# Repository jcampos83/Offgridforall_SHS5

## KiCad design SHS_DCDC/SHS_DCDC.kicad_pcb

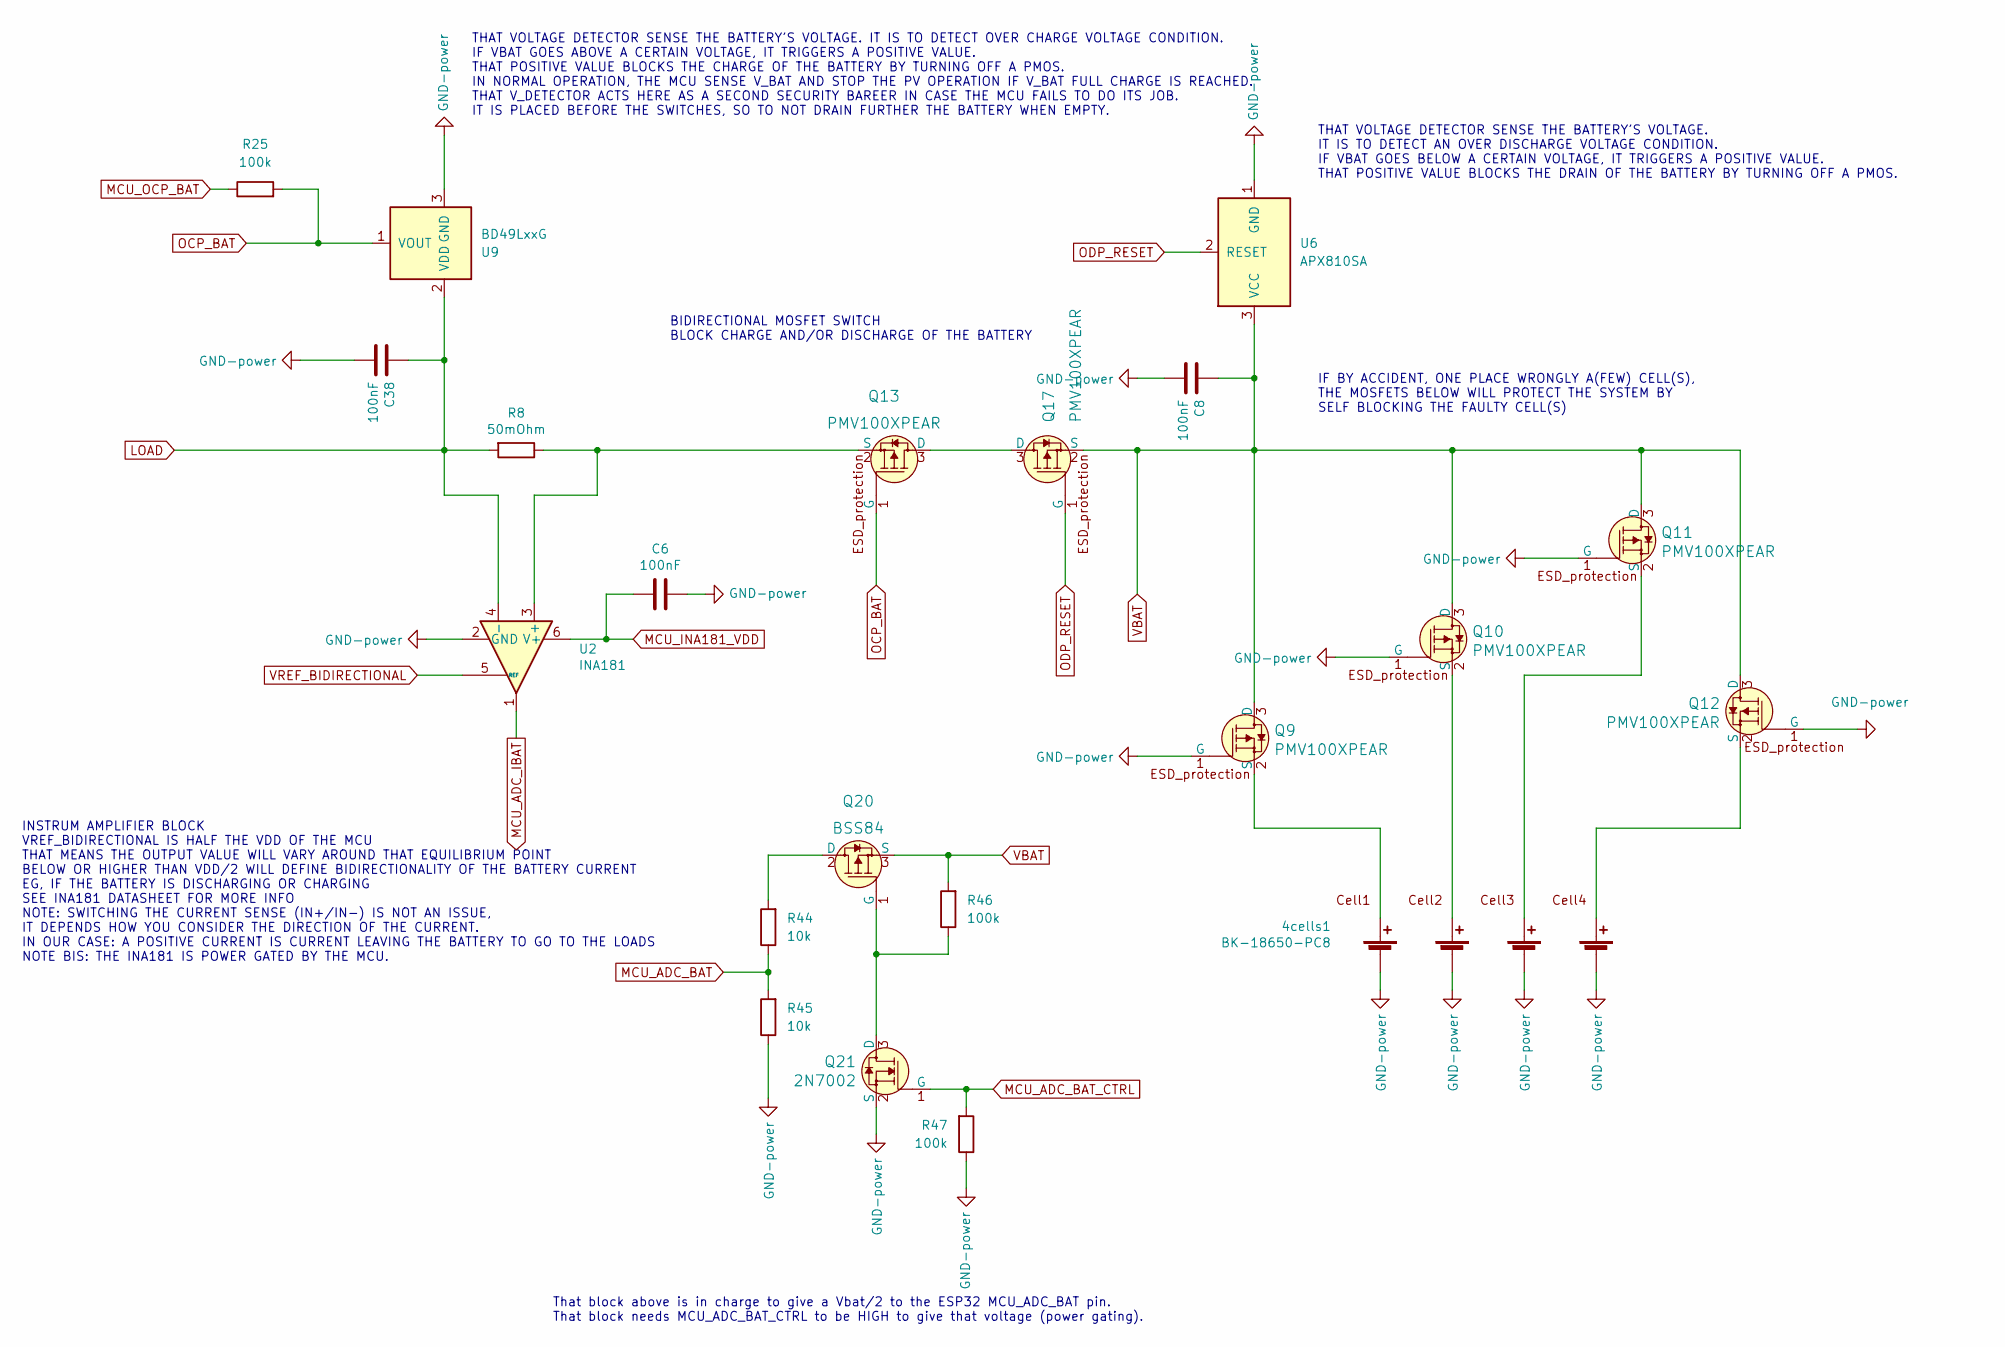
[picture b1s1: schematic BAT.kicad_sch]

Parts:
4cells1: BK-18650-PC8
C6, C8, C38: 100nF; C_0402_1005Metric
Q9, Q10, Q11, Q12, Q13, Q17: PMV100XPEAR; SOT-23-3; MPN PMV100XPEAR
Q20: BSS84; SOT-23; MPN BSS84; Digi-Key_PN BSS84CT-ND
Q21: 2N7002; SOT-23; MPN 2N7002; Digi-Key_PN 2N7002NCT-ND
R8: 50mOhm; R_2010_5025Metric
R25, R46, R47: 100k; R_0402_1005Metric
R44, R45: 10k; R_0402_1005Metric
U2: INA181; SOT-23-6
U6: APX810SA; SOT-23
U9: BD49LxxG; SOT-23

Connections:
GND: 4cells1.2 (-), 4cells1.4 (-), 4cells1.6 (-), 4cells1.8 (-), C6.1, C8.2, C38.2, Q9.1 (G), Q10.1 (G), Q11.1 (G), Q12.1 (G), Q21.2 (S), R45.1, R47.1, U2.2 (GND), U6.1 (GND), U9.3 (GND); also elsewhere on the board
LOAD: C38.1, R8.2, U2.4 (-), U9.2 (VDD); also elsewhere on the board
MCU_ADC_BAT: R44.1, R45.2; also elsewhere on the board
MCU_ADC_BAT_CTRL: Q21.1 (G), R47.2; also elsewhere on the board
MCU_ADC_IBAT: U2.1; also elsewhere on the board
MCU_INA181_VDD: C6.2, U2.6 (V+); also elsewhere on the board
MCU_OCP_BAT: R25.1; also elsewhere on the board
unnamed: 4cells1.1 (+), Q9.2 (S)
unnamed: 4cells1.3 (+), Q10.2 (S)
unnamed: 4cells1.5 (+), Q11.2 (S)
unnamed: 4cells1.7 (+), Q12.2 (S)
unnamed: Q13.2 (S), R8.1, U2.3 (+)
unnamed: Q13.3 (D), Q17.3 (D)
unnamed: Q20.1 (G), Q21.3 (D), R46.1
unnamed: Q20.2 (D), R44.2
OCP_BAT: Q13.1 (G), R25.2, U9.1 (VOUT)
ODP_RESET: Q17.1 (G), U6.2 (RESET); also elsewhere on the board
VBAT: C8.1, Q9.3 (D), Q10.3 (D), Q11.3 (D), Q12.3 (D), Q17.2 (S), Q20.3 (S), R46.2, U6.3 (VCC)
VREF_BIDIRECTIONAL: U2.5 (REF); also elsewhere on the board

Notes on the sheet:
IF BY ACCIDENT, ONE PLACE WRONGLY A(FEW) CELL(S), THE MOSFETS BELOW WILL PROTECT THE SYSTEM BY SELF BLOCKING THE FAULTY CELL(S)
BIDIRECTIONAL MOSFET SWITCH BLOCK CHARGE AND/OR DISCHARGE OF THE BATTERY
THAT VOLTAGE DETECTOR SENSE THE BATTERY'S VOLTAGE. IT IS TO DETECT AN OVER DISCHARGE VOLTAGE CONDITION. IF VBAT GOES BELOW A CERTAIN VOLTAGE, IT TRIGGERS A POSITIVE VALUE. THAT POSITIVE VALUE BLOCKS THE DRAIN OF THE BATTERY BY TURNING OFF A PMOS.
That block above is in charge to give a Vbat/2 to the ESP32 MCU_ADC_BAT pin. That block needs MCU_ADC_BAT_CTRL to be HIGH to give that voltage (power gating).
THAT VOLTAGE DETECTOR SENSE THE BATTERY'S VOLTAGE. IT IS TO DETECT OVER CHARGE VOLTAGE CONDITION. IF VBAT GOES ABOVE A CERTAIN VOLTAGE, IT TRIGGERS A POSITIVE VALUE. THAT POSITIVE VALUE BLOCKS THE CHARGE OF THE BATTERY BY TURNING OFF A PMOS. IN NORMAL OPERATION, THE MCU SENSE V_BAT AND STOP THE PV 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
INSTRUM AMPLIFIER BLOCK VREF_BIDIRECTIONAL IS HALF THE VDD OF THE MCU THAT MEANS THE OUTPUT VALUE WILL VARY AROUND THAT EQUILIBRIUM POINT BELOW OR HIGHER THAN VDD/2 WILL DEFINE BIDIRECTIONALITY OF THE BATTERY CURRENT EG, IF THE BATTERY IS DISCHARGING OR CHARGING SEE INA181 DATASHEET FOR MORE INFO N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

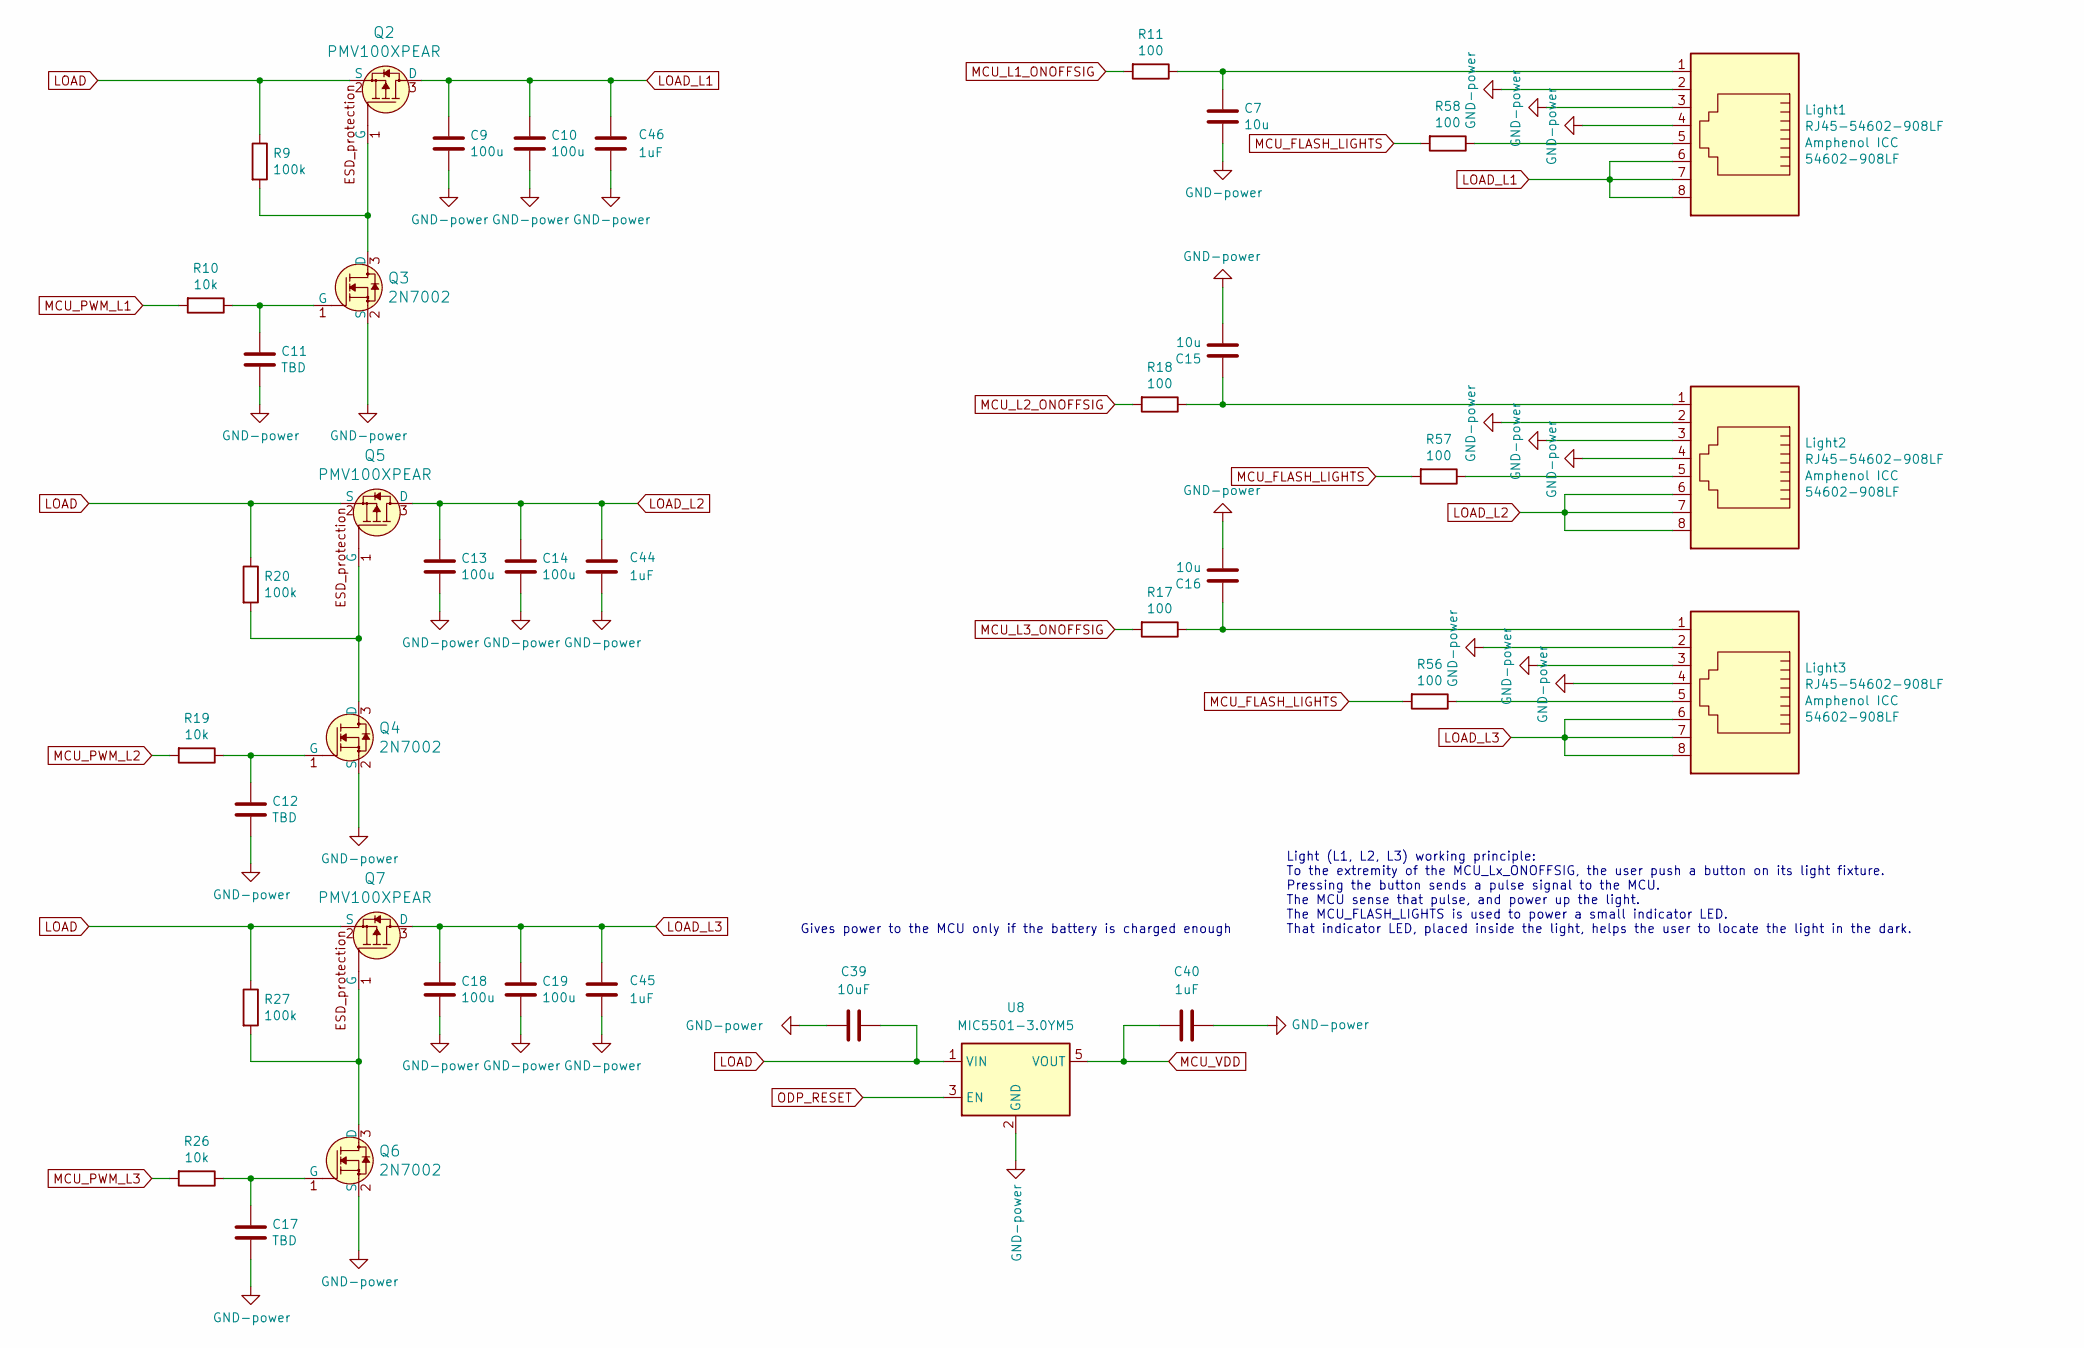
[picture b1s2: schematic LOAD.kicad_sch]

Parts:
C7, C15, C16: 10u; C_0603_1608Metric
C9, C10, C13, C14, C18, C19: 100u; C_1210_3225Metric
C11, C12, C17: TBD; C_0603_1608Metric
C39: 10uF; C_0805_2012Metric
C40: 1uF; C_0603_1608Metric
C44, C45, C46: 1uF; C_0402_1005Metric
Light1, Light2, Light3: RJ45-54602-908LF; RJ45_Amphenol_54602-x08_Horizontal
Q2, Q5, Q7: PMV100XPEAR; SOT-23-3; MPN PMV100XPEAR
Q3, Q4, Q6: 2N7002; SOT-23-3; MPN 2N7002; Digi-Key_PN 2N7002NCT-ND
R9, R20, R27: 100k; R_0603_1608Metric
R10, R19, R26: 10k; R_0603_1608Metric
R11, R17, R18, R56, R57, R58: 100; R_0603_1608Metric
U8: MIC5501-3.0YM5; SOT-23-5

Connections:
GND: C7.2, C9.2, C10.2, C11.2, C12.2, C13.2, C14.2, C15.2, C16.2, C17.2, C18.2, C19.2, C39.1, C40.2, C44.2, C45.2, C46.2, Light1.2, Light1.3, Light1.4, Light2.2, Light2.3, Light2.4, Light3.2, Light3.3, Light3.4, Q3.2 (S), Q4.2 (S), Q6.2 (S), U8.2 (GND); also elsewhere on the board
LOAD: C39.2, Q2.2 (S), Q5.2 (S), Q7.2 (S), R9.1, R20.1, R27.1, U8.1 (VIN); also elsewhere on the board
LOAD_L1: C9.1, C10.1, C46.1, Light1.6, Light1.7, Light1.8, Q2.3 (D)
LOAD_L2: C13.1, C14.1, C44.1, Light2.6, Light2.7, Light2.8, Q5.3 (D)
LOAD_L3: C18.1, C19.1, C45.1, Light3.6, Light3.7, Light3.8, Q7.3 (D)
MCU_FLASH_LIGHTS: R56.2, R57.2, R58.2; also elsewhere on the board
MCU_L1_ONOFFSIG: R11.2; also elsewhere on the board
MCU_L2_ONOFFSIG: R18.2; also elsewhere on the board
MCU_L3_ONOFFSIG: R17.2; also elsewhere on the board
MCU_PWM_L1: R10.2; also elsewhere on the board
MCU_PWM_L2: R19.2; also elsewhere on the board
MCU_PWM_L3: R26.2; also elsewhere on the board
MCU_VDD: C40.1, U8.5 (VOUT); also elsewhere on the board
unnamed: C7.1, Light1.1, R11.1
unnamed: C11.1, Q3.1 (G), R10.1
unnamed: C12.1, Q4.1 (G), R19.1
unnamed: C15.1, Light2.1, R18.1
unnamed: C16.1, Light3.1, R17.1
unnamed: C17.1, Q6.1 (G), R26.1
unnamed: Light1.5, R58.1
unnamed: Light2.5, R57.1
unnamed: Light3.5, R56.1
unnamed: Q2.1 (G), Q3.3 (D), R9.2
unnamed: Q4.3 (D), Q5.1 (G), R20.2
unnamed: Q6.3 (D), Q7.1 (G), R27.2
ODP_RESET: U8.3 (EN); also elsewhere on the board

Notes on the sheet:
Light (L1, L2, L3) working principle: To the extremity of the MCU_Lx_ONOFFSIG, the user push a button on its light fixture. Pressing the button sends a pulse signal to the MCU. The MCU sense that pulse, and power up the light. The MCU_FLASH_LIGHTS is used to power a small indicator LED. That indica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
Gives power to the MCU only if the battery is charged enough

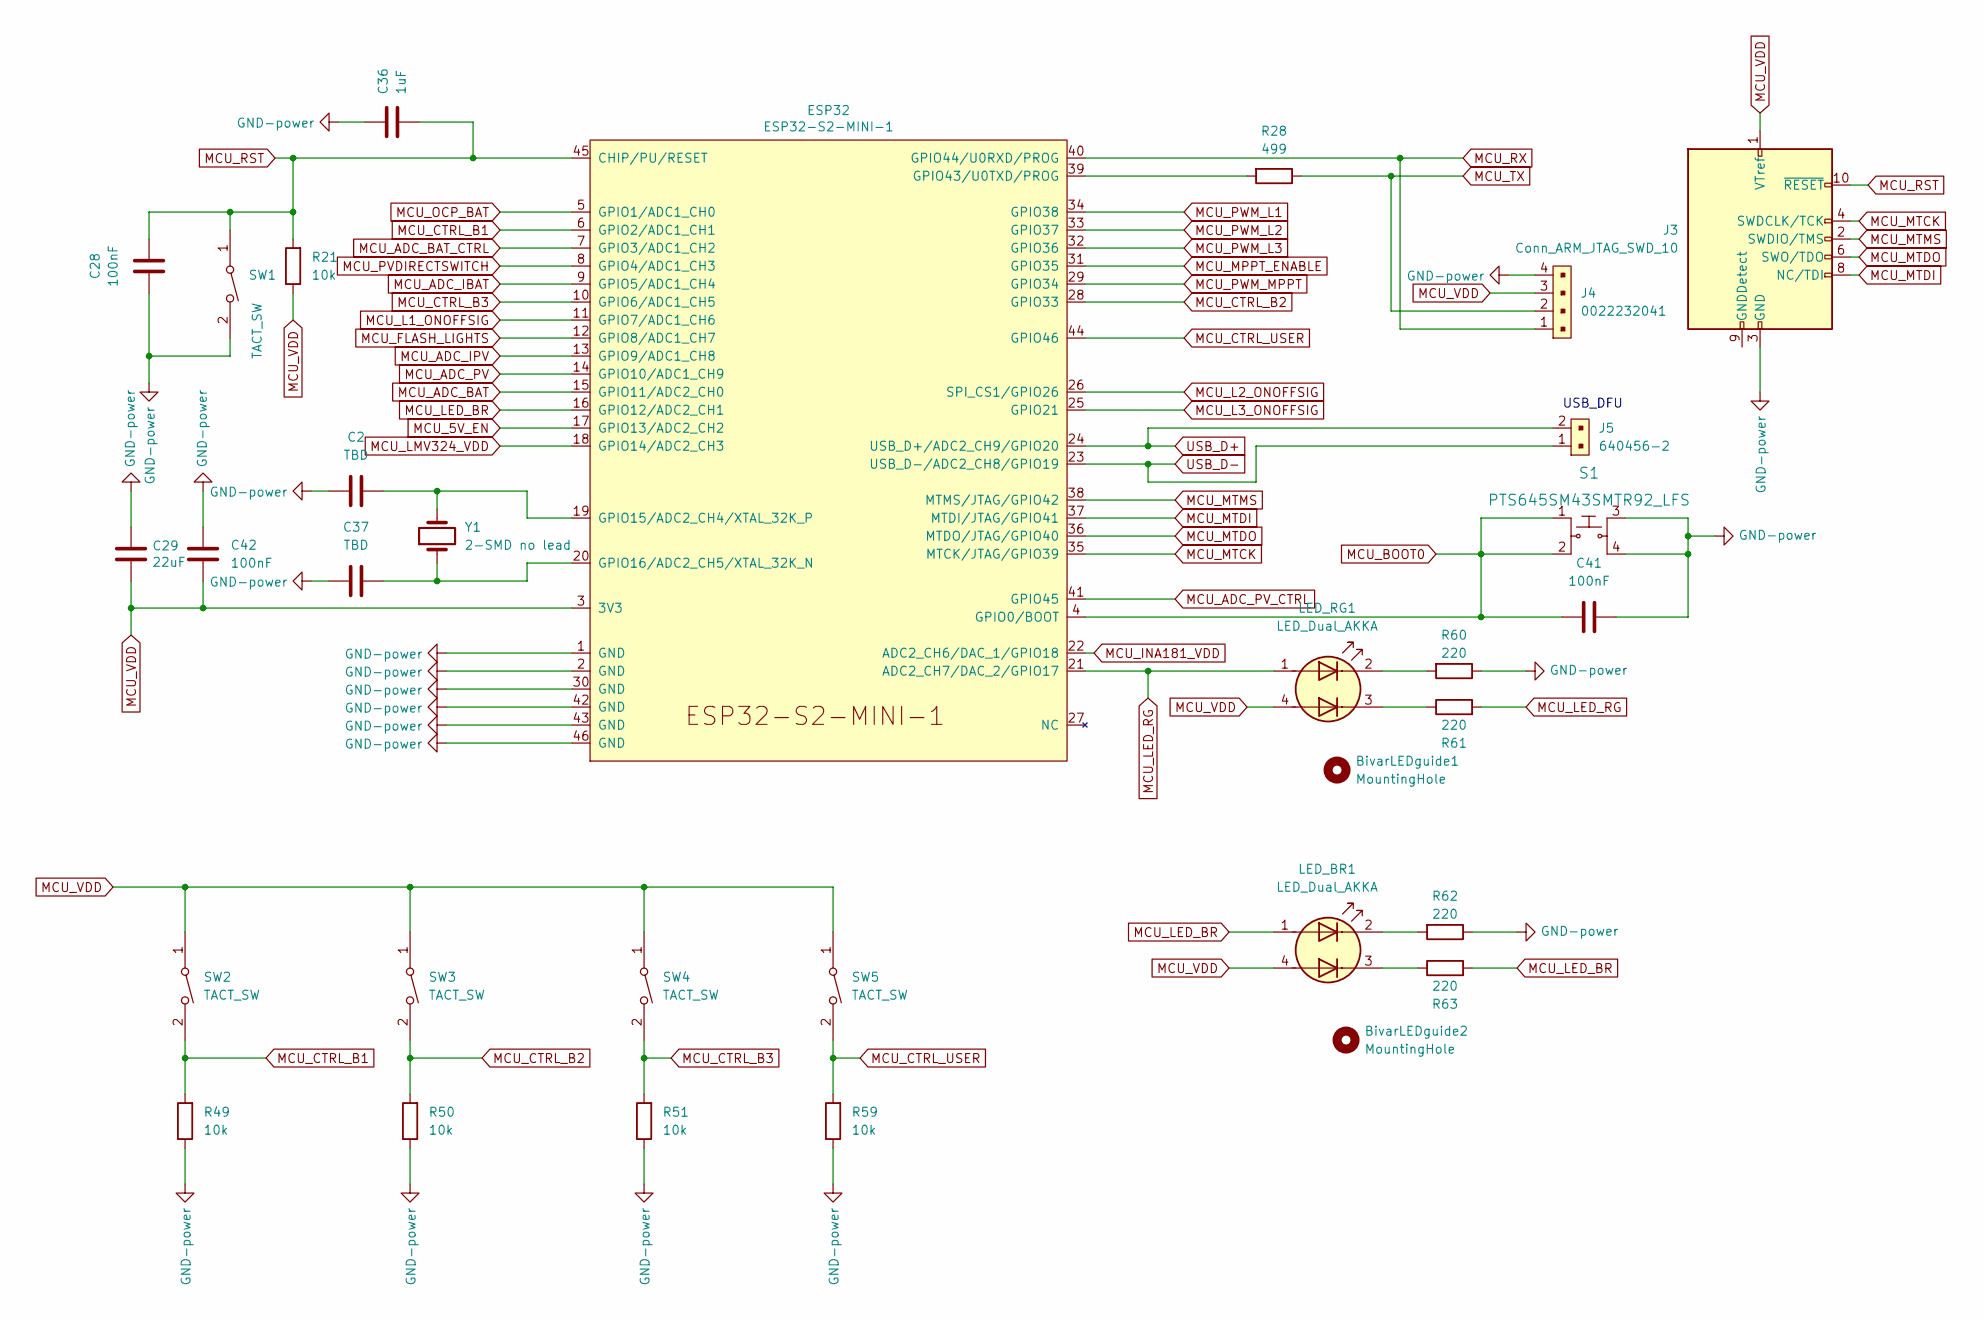
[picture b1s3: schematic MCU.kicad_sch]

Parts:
BivarLEDguide1, BivarLEDguide2: MountingHole; BIVAR VLP-XXX-F
C2, C37: TBD; C_0402_1005Metric
C28, C41, C42: 100nF; C_0402_1005Metric
C29: 22uF; C_0603_1608Metric
C36: 1uF; C_0402_1005Metric
ESP32: ESP32-S2-MINI-1
J3: Conn_ARM_JTAG_SWD_10; PinHeader_2x05_P1.27mm_Vertical
J4: 0022232041; PinHeader_1x4_P2.54mm_Drill1.02mm; MPN 0022232041; Digi-Key_PN WM4202-ND
J5: 640456-2; PinHeader_1x2_P2.54mm_Drill1.02mm; MPN 640456-2; Digi-Key_PN A1921-ND
LED_BR1: LED_Dual_AKKA; LED_Kingbright_APHBM2012_2x1.25mm
LED_RG1: LED_Dual_AKKA; LED_Kingbright_APHBM2012_2x1.25mm
R21, R49, R50, R51, R59: 10k; R_0402_1005Metric
R28: 499; R_0402_1005Metric
R60, R61, R62, R63: 220; R_0402_1005Metric
S1: PTS645SM43SMTR92_LFS; Switch_Tactile_SMD_6x6mm_PTS645; MPN PTS645SM43SMTR92 LFS; Digi-Key_PN CKN9112CT-ND
SW1, SW2, SW3, SW4, SW5: TACT_SW; ESWITCH_TL1105
Y1: 2-SMD no lead; Crystal_SMD_3215-2Pin_3.2x1.5mm

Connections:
GND: C2.2, C28.2, C29.1, C36.2, C37.2, C41.1, C42.1, ESP32.1 (GND), ESP32.2 (GND), ESP32.30 (GND), ESP32.42 (GND), ESP32.43 (GND), ESP32.46 (GND), J3.3 (GND), J3.5 (GND), J4.4, R49.1, R50.1, R51.1, R59.1, R60.1, R62.1, S1.3, S1.4, SW1.2; also elsewhere on the board
MCU_5V_EN: ESP32.17 (GPIO13/ADC2_CH2); also elsewhere on the board
MCU_ADC_BAT: ESP32.15 (GPIO11/ADC2_CH0); also elsewhere on the board
MCU_ADC_BAT_CTRL: ESP32.7 (GPIO3/ADC1_CH2); also elsewhere on the board
MCU_ADC_IBAT: ESP32.9 (GPIO5/ADC1_CH4); also elsewhere on the board
MCU_ADC_IPV: ESP32.13 (GPIO9/ADC1_CH8); also elsewhere on the board
MCU_ADC_PV: ESP32.14 (GPIO10/ADC1_CH9); also elsewhere on the board
MCU_ADC_PV_CTRL: ESP32.41 (GPIO45); also elsewhere on the board
MCU_BOOT0: C41.2, ESP32.4 (GPIO0/BOOT), S1.1, S1.2
MCU_CTRL_B1: ESP32.6 (GPIO2/ADC1_CH1), R49.2, SW2.2
MCU_CTRL_B2: ESP32.28 (GPIO33), R50.2, SW3.2
MCU_CTRL_B3: ESP32.10 (GPIO6/ADC1_CH5), R51.2, SW4.2
MCU_CTRL_USER: ESP32.44 (GPIO46), R59.2, SW5.2
MCU_FLASH_LIGHTS: ESP32.12 (GPIO8/ADC1_CH7); also elsewhere on the board
MCU_INA181_VDD: ESP32.22 (ADC2_CH6/DAC_1/GPIO18); also elsewhere on the board
MCU_L1_ONOFFSIG: ESP32.11 (GPIO7/ADC1_CH6); also elsewhere on the board
MCU_L2_ONOFFSIG: ESP32.26 (SPI_CS1/GPIO26); also elsewhere on the board
MCU_L3_ONOFFSIG: ESP32.25 (GPIO21); also elsewhere on the board
MCU_LED_BR: ESP32.16 (GPIO12/ADC2_CH1), LED_BR1.1 (A1), R63.2
MCU_LED_RG: ESP32.21 (ADC2_CH7/DAC_2/GPIO17), LED_RG1.1 (A1), R61.2
MCU_LMV324_VDD: ESP32.18 (GPIO14/ADC2_CH3); also elsewhere on the board
MCU_MPPT_ENABLE: ESP32.31 (GPIO35); also elsewhere on the board
MCU_MTCK: ESP32.35 (MTCK/JTAG/GPIO39), J3.4 (SWDCLK/TCK)
MCU_MTDI: ESP32.37 (MTDI/JTAG/GPIO41), J3.8 (NC/TDI)
MCU_MTDO: ESP32.36 (MTDO/JTAG/GPIO40), J3.6 (SWO/TDO)
MCU_MTMS: ESP32.38 (MTMS/JTAG/GPIO42), J3.2 (SWDIO/TMS)
MCU_OCP_BAT: ESP32.5 (GPIO1/ADC1_CH0); also elsewhere on the board
MCU_PVDIRECTSWITCH: ESP32.8 (GPIO4/ADC1_CH3); also elsewhere on the board
MCU_PWM_L1: ESP32.34 (GPIO38); also elsewhere on the board
MCU_PWM_L2: ESP32.33 (GPIO37); also elsewhere on the board
MCU_PWM_L3: ESP32.32 (GPIO36); also elsewhere on the board
MCU_PWM_MPPT: ESP32.29 (GPIO34); also elsewhere on the board
MCU_RST: C28.1, C36.1, ESP32.45 (CHIP/PU/RESET), J3.10 (~RESET), R21.2, SW1.1
MCU_RX: ESP32.40 (GPIO44/U0RXD/PROG), J4.1
MCU_TX: J4.2, R28.1
MCU_VDD: C29.2, C42.2, ESP32.3 (3V3), J3.1 (VTref), J4.3, LED_BR1.4 (A2), LED_RG1.4 (A2), R21.1, SW2.1, SW3.1, SW4.1, SW5.1; also elsewhere on the board
unnamed: C2.1, ESP32.19 (GPIO15/ADC2_CH4/XTAL_32K_P), Y1.2
unnamed: C37.1, ESP32.20 (GPIO16/ADC2_CH5/XTAL_32K_N), Y1.1
unnamed: ESP32.39 (GPIO43/U0TXD/PROG), R28.2
unnamed: LED_BR1.2 (K1), R62.2
unnamed: LED_BR1.3 (K2), R63.1
unnamed: LED_RG1.2 (K1), R60.2
unnamed: LED_RG1.3 (K2), R61.1
USB_D+: ESP32.24 (USB_D+/ADC2_CH9/GPIO20), J5.2; also elsewhere on the board
USB_D-: ESP32.23 (USB_D-/ADC2_CH8/GPIO19), J5.1; also elsewhere on the board

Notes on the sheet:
USB_DFU

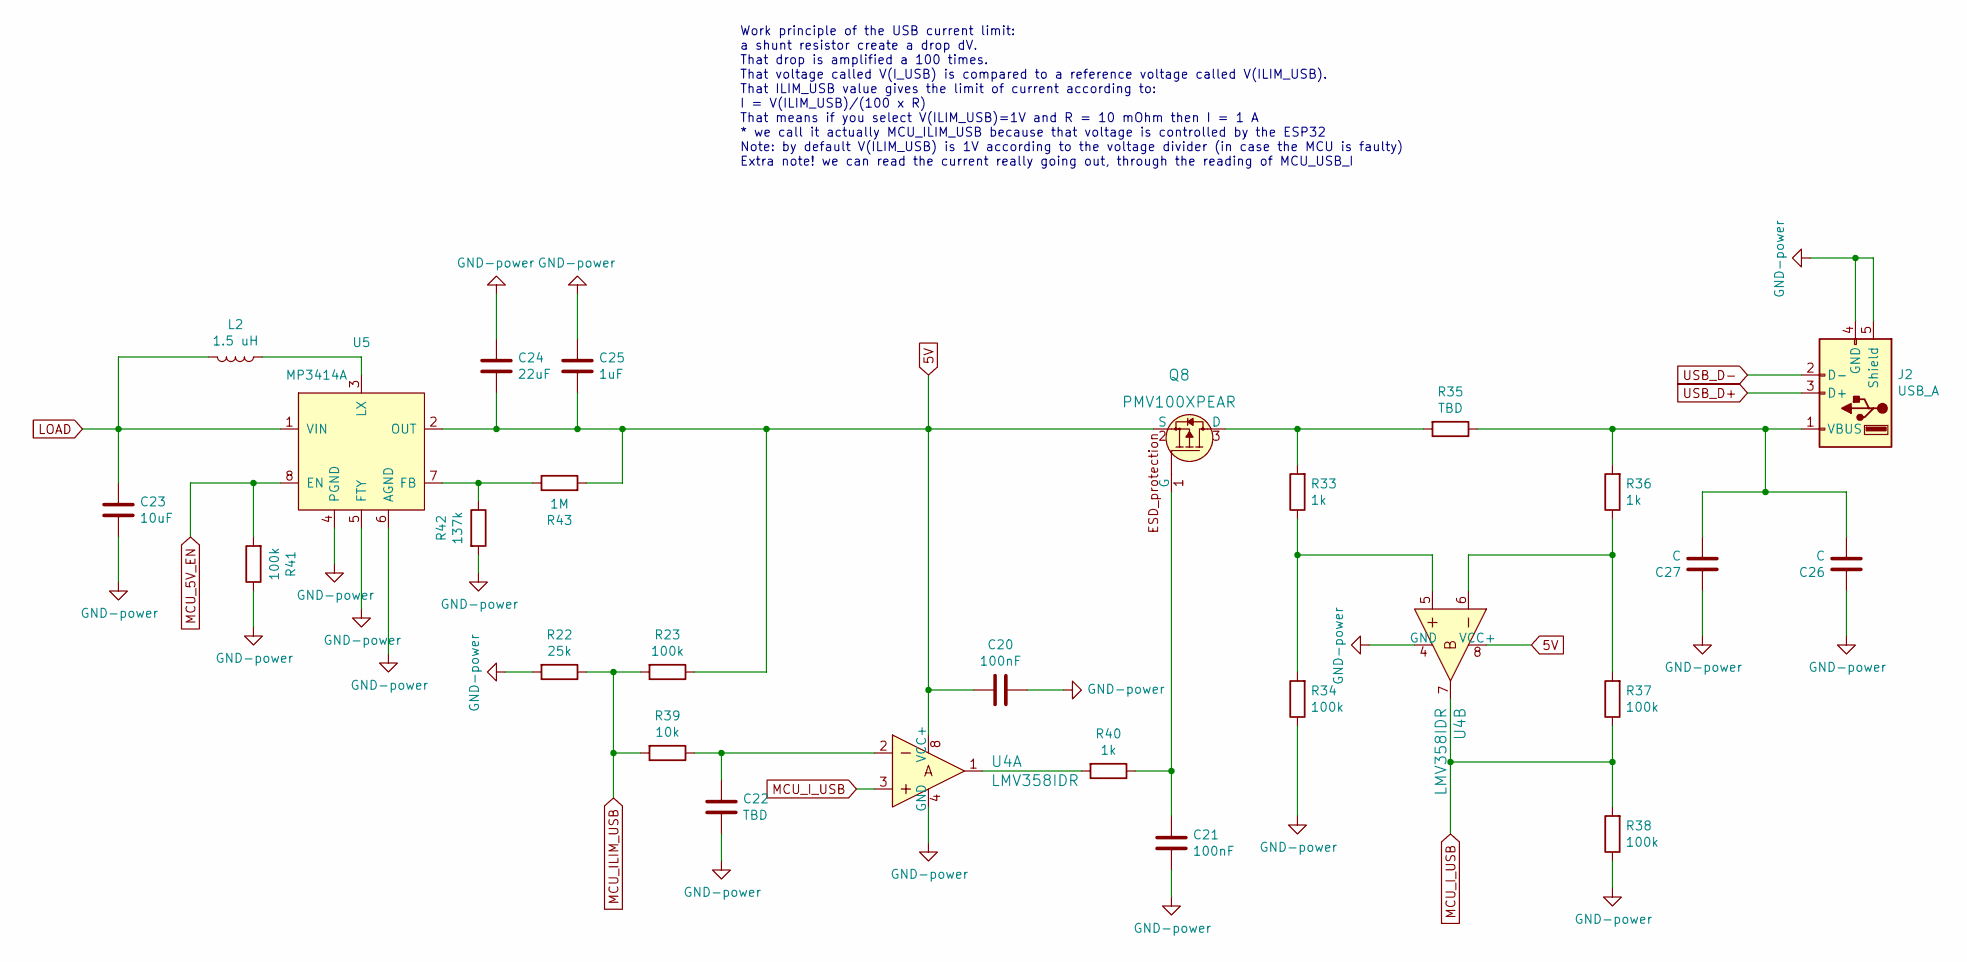
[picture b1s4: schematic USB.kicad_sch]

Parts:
C20: 100nF; C_0402_1005Metric
C21: 100nF; C_0603_1608Metric
C22: TBD; C_0603_1608Metric
C23: 10uF; C_0805_2012Metric
C24: 22uF; C_0805_2012Metric
C25: 1uF; C_0603_1608Metric
C26, C27: C; C_1210_3225Metric
J2: USB_A; USB_A_CONNFLY_DS1095-WNR0
L2: 1.5 uH; L_Taiyo-Yuden_NR-60xx
Q8: PMV100XPEAR; SOT-23-3; MPN PMV100XPEAR
R22: 25k; R_0603_1608Metric
R23, R34, R37, R38, R41: 100k; R_0603_1608Metric
R33, R36, R40: 1k; R_0603_1608Metric
R35: TBD; R_0805_2012Metric
R39: 10k; R_0603_1608Metric
R42: 137k; R_0603_1608Metric
R43: 1M; R_0603_1608Metric
U4: LMV358IDR; SOIC-8_W3.9mm; MPN LMV358IDR; Digi-Key_PN 296-9571-1-ND
U5: MP3414A

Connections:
5V: C20.2, C24.2, C25.2, Q8.2 (S), R23.1, R43.2, U4.8 (VCC+), U5.2 (OUT); also elsewhere on the board
GND: C20.1, C21.1, C22.2, C23.2, C24.1, C25.1, C26.1, C27.1, J2.4 (GND), J2.5 (Shield), R22.2, R34.1, R38.1, R41.1, R42.2, U4.4 (GND), U5.4 (PGND), U5.5 (FTY), U5.6 (AGND); also elsewhere on the board
LOAD: C23.1, L2.2, U5.1 (VIN); also elsewhere on the board
MCU_5V_EN: R41.2, U5.8 (EN); also elsewhere on the board
MCU_ILIM_USB: R22.1, R23.2, R39.2
MCU_I_USB: R37.1, R38.2, U4.3, U4.7
unnamed: C21.2, Q8.1 (G), R40.1
unnamed: C22.1, R39.1, U4.2
unnamed: C26.2, C27.2, J2.1 (VBUS), R35.1, R36.2
unnamed: L2.1, U5.3 (LX)
unnamed: Q8.3 (D), R33.2, R35.2
unnamed: R33.1, R34.2, U4.5
unnamed: R36.1, R37.2, U4.6
unnamed: R40.2, U4.1
unnamed: R42.1, R43.1, U5.7 (FB)
USB_D+: J2.3 (D+); also elsewhere on the board
USB_D-: J2.2 (D-); also elsewhere on the board

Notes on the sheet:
Work principle of the USB current limit: a shunt resistor create a drop dV. That drop is amplified a 100 times. That voltage called V(I_USB) is compared to a reference voltage called V(ILIM_USB). That ILIM_USB value gives the limit of current according to: I = V(ILIM_USB)/(100 x R) That means if yo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

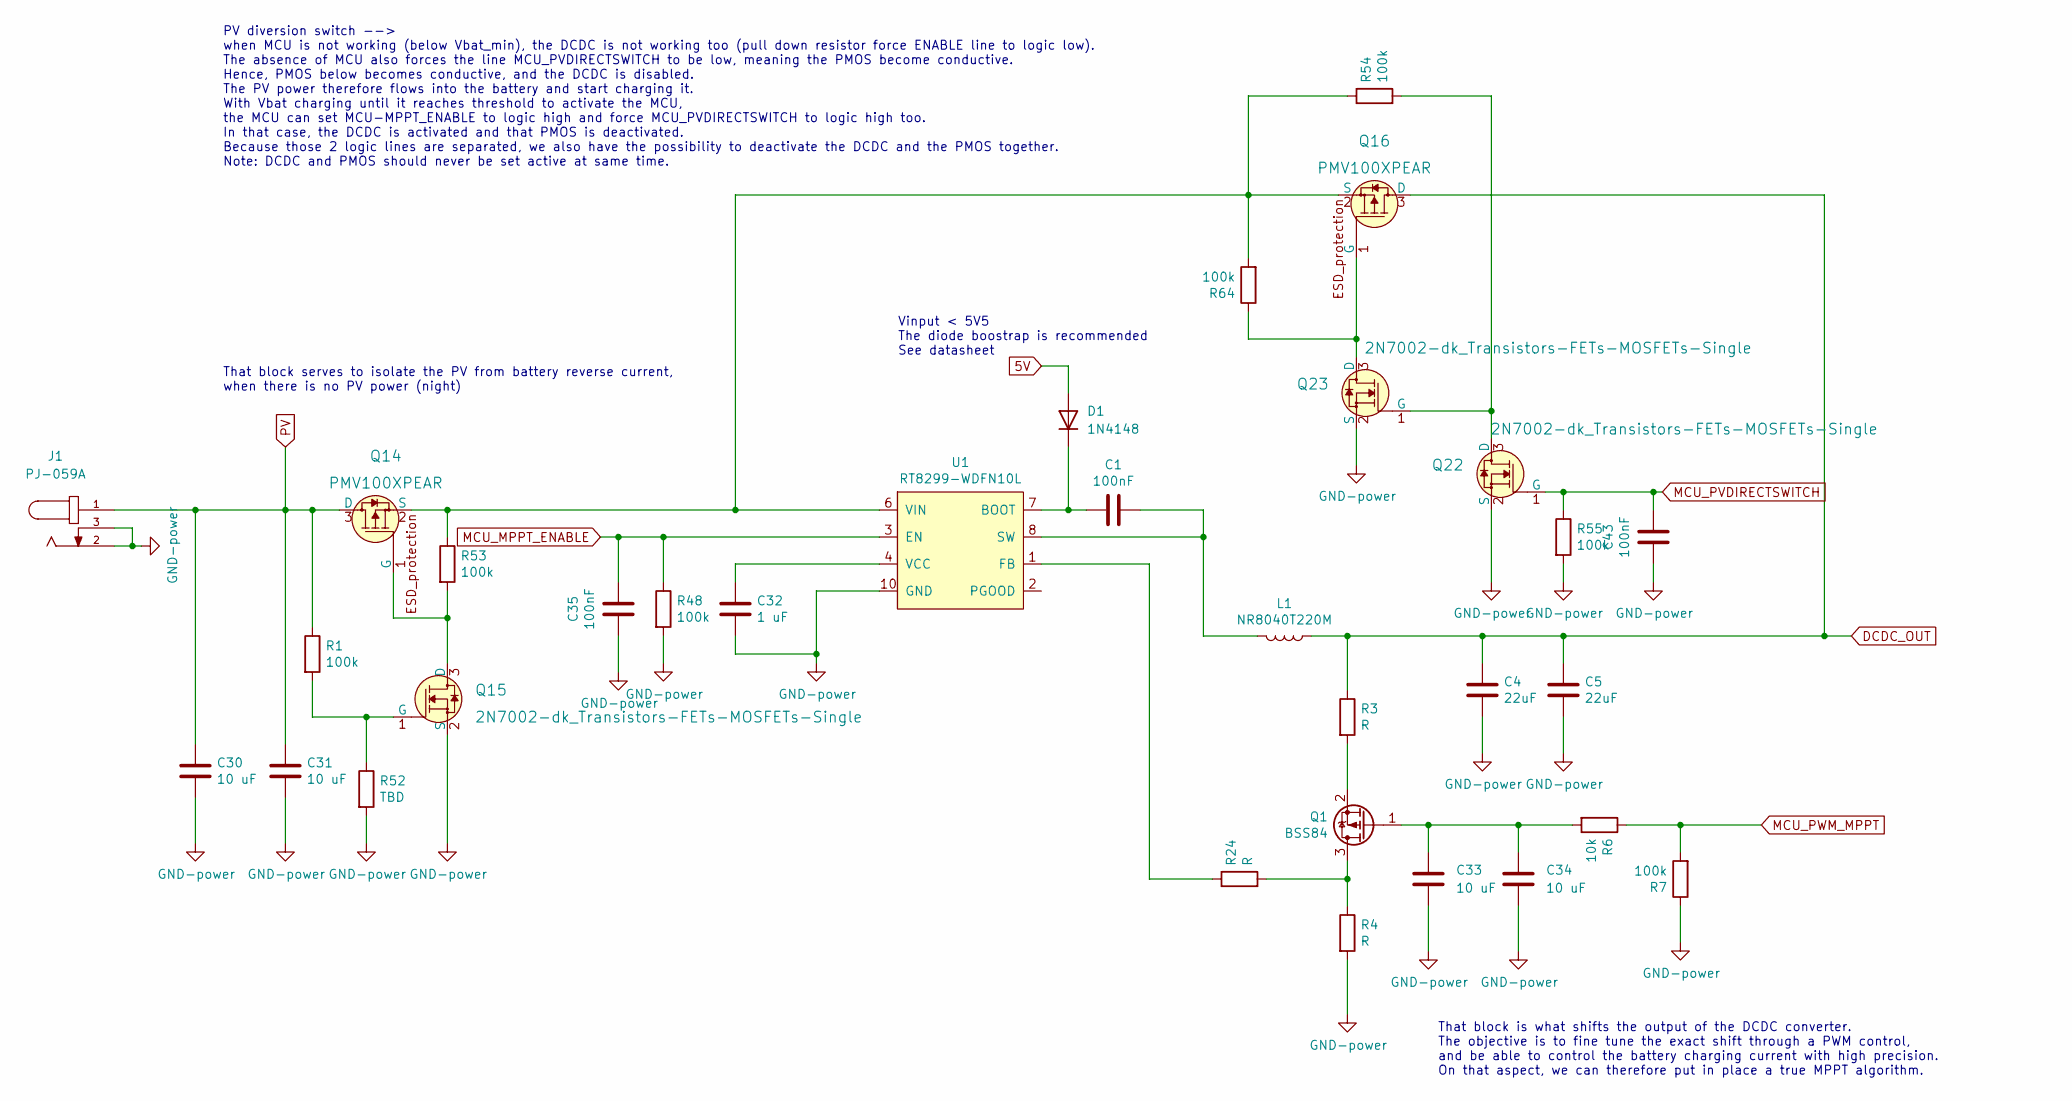
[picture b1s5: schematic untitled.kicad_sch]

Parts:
C1, C35, C43: 100nF; C_0402_1005Metric
C4, C5: 22uF; C_0805_2012Metric
C30, C31: 10 uF; C_0805_2012Metric
C32: 1 uF; C_0402_1005Metric
C33, C34: 10 uF; C_0603_1608Metric
D1: 1N4148; D_SOD-123
J1: PJ-059A; CUI_PJ-059A; PARTREV 1.02
L1: NR8040T220M; L_Taiyo-Yuden_NR-80xx
Q1: BSS84; SOT-23
Q14, Q16: PMV100XPEAR; SOT-23-3; MPN PMV100XPEAR
Q15, Q22, Q23: 2N7002-dk_Transistors-FETs-MOSFETs-Single; SOT-23-3; MPN 2N7002; Digi-Key_PN 2N7002NCT-ND
R1, R7, R48, R53, R54, R55, R64: 100k; R_0402_1005Metric
R3, R4, R24: R; R_0402_1005Metric
R6: 10k; R_0402_1005Metric
R52: TBD; R_0402_1005Metric
U1: RT8299-WDFN10L; RT8299-WDFN

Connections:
5V: D1.2 (A); also elsewhere on the board
DCDC_OUT: C4.1, C5.1, L1.1, Q16.3 (D), R3.1; also elsewhere on the board
GND: C4.2, C5.2, C30.2, C31.2, C32.2, C33.2, C34.2, C35.1, C43.1, J1.2, J1.3, Q15.2 (S), Q22.2 (S), Q23.2 (S), R4.2, R7.1, R48.2, R52.2, R55.2, U1.10 (GND); also elsewhere on the board
MCU_MPPT_ENABLE: C35.2, R48.1, U1.3 (EN); also elsewhere on the board
MCU_PVDIRECTSWITCH: C43.2, Q22.1 (G), R55.1; also elsewhere on the board
MCU_PWM_MPPT: R6.1, R7.2; also elsewhere on the board
unnamed: C1.1, D1.1 (K), U1.7 (BOOT)
unnamed: C1.2, L1.2, U1.8 (SW)
unnamed: C32.1, U1.4 (VCC)
unnamed: C33.1, C34.1, Q1.1 (G), R6.2
unnamed: Q1.2 (S), R3.2
unnamed: Q1.3 (D), R4.1, R24.2
unnamed: Q14.1 (G), Q15.3 (D), R53.2
unnamed: Q14.2 (S), Q16.2 (S), R53.1, R54.1, R64.2, U1.6 (VIN)
unnamed: Q15.1 (G), R1.2, R52.1
unnamed: Q16.1 (G), Q23.3 (D), R64.1
unnamed: Q22.3 (D), Q23.1 (G), R54.2
unnamed: R24.1, U1.1 (FB)
PV: C30.1, C31.1, J1.1, Q14.3 (D), R1.1; also elsewhere on the board

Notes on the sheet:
That block is what shifts the output of the DCDC converter. The objective is to fine tune the exact shift through a PWM control, and be able to control the battery charging current with high precision. On that aspect, we can therefore put in place a true MPPT algorithm.
PV diversion switch --> when MCU is not working (below Vbat_min), the DCDC is not working too (pull down resistor force ENABLE line to logic low). The absence of MCU also forces the line MCU_PVDIRECTSWITCH to be low, meaning the PMOS become conductive. Hence, PMOS below becomes conductive, and the 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
Vinput < 5V5 The diode boostrap is recommended See datasheet
That block serves to isolate the PV from battery reverse current, when there is no PV power (night)

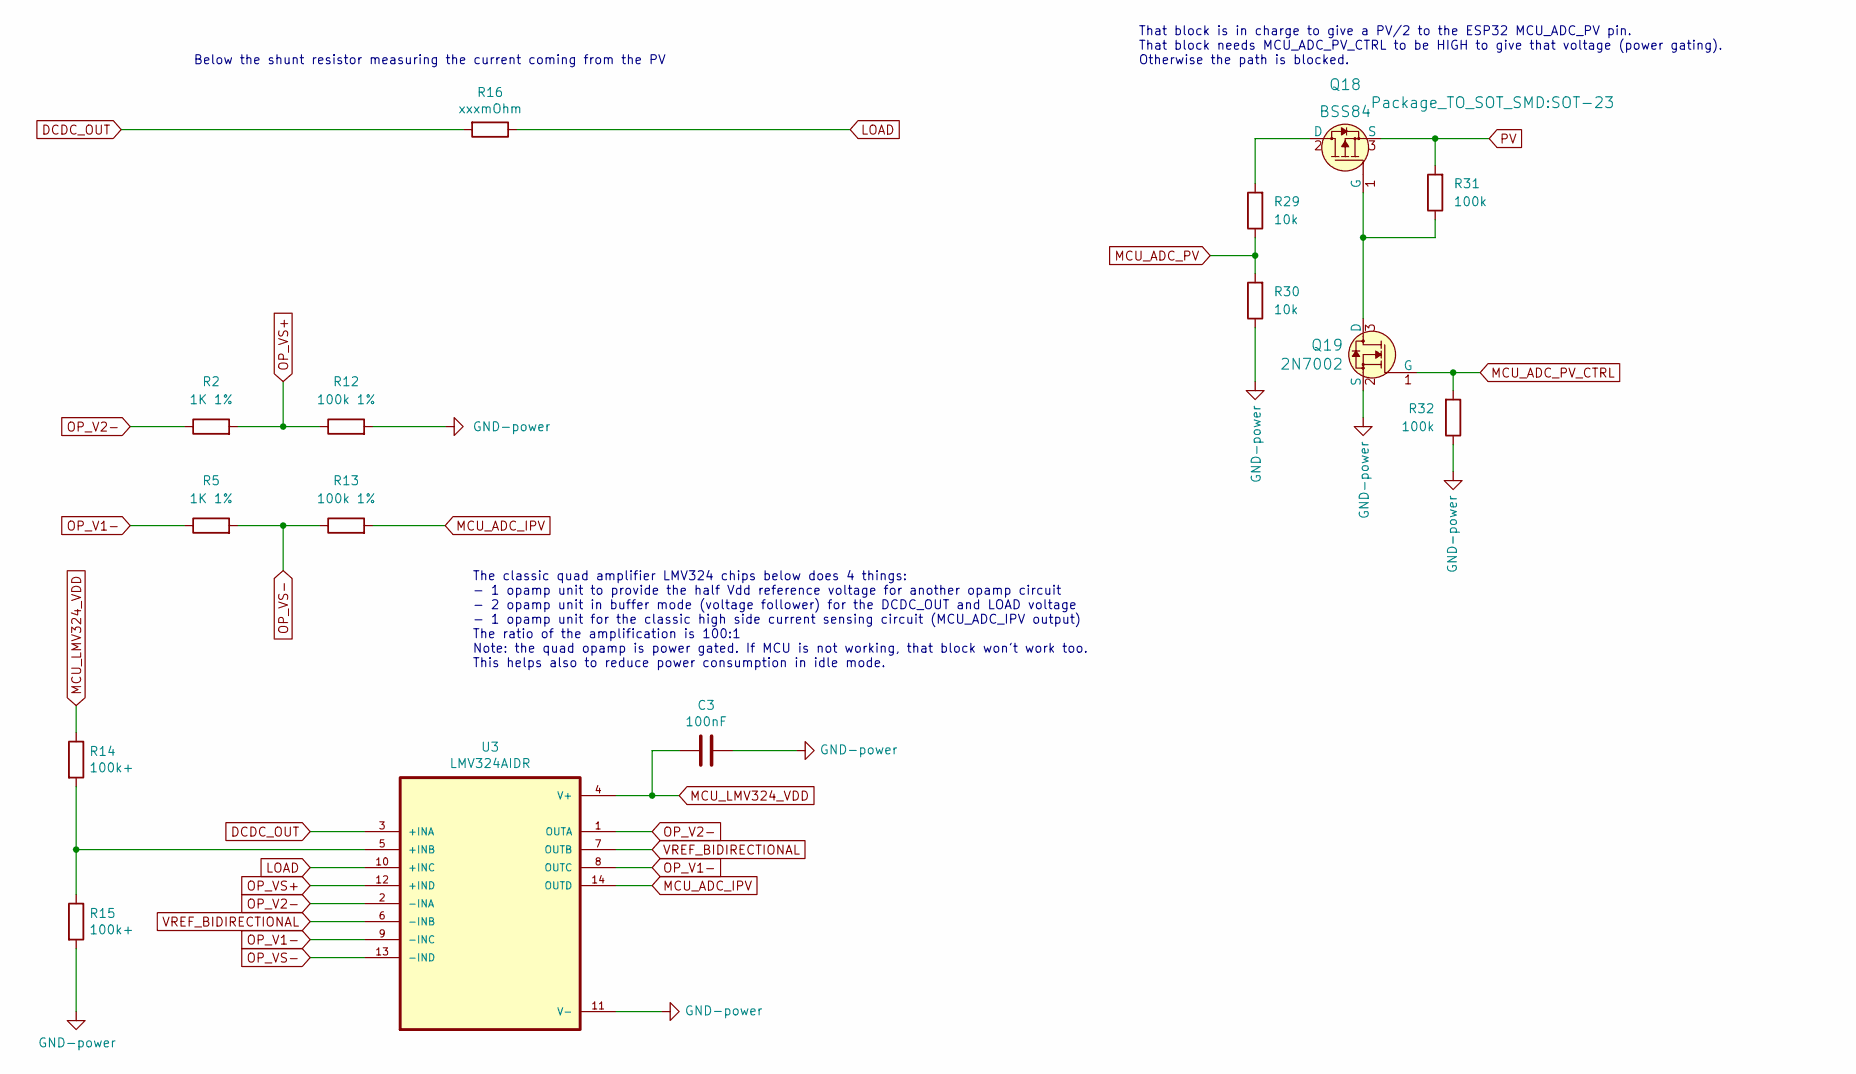
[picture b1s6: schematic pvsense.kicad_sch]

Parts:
C3: 100nF; C_0402_1005Metric
Q18: BSS84; SOT-23; MPN BSS84; Digi-Key_PN BSS84CT-ND
Q19: 2N7002; SOT-23; MPN 2N7002; Digi-Key_PN 2N7002NCT-ND
R2, R5: 1K 1%; R_0402_1005Metric
R12, R13: 100k 1%; R_0402_1005Metric
R14, R15: 100k+; R_0603_1608Metric
R16: xxxmOhm; R_1206_3216Metric
R29, R30: 10k; R_0402_1005Metric
R31, R32: 100k; R_0402_1005Metric
U3: LMV324AIDR; SOIC127P600X175-14N

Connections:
DCDC_OUT: R16.2, U3.3 (+INA); also elsewhere on the board
GND: C3.1, Q19.2 (S), R12.2, R15.2, R30.1, R32.1, U3.11 (V-); also elsewhere on the board
LOAD: R16.1, U3.10 (+INC); also elsewhere on the board
MCU_ADC_IPV: R13.2, U3.14 (OUTD); also elsewhere on the board
MCU_ADC_PV: R29.1, R30.2; also elsewhere on the board
MCU_ADC_PV_CTRL: Q19.1 (G), R32.2; also elsewhere on the board
MCU_LMV324_VDD: C3.2, R14.1, U3.4 (V+); also elsewhere on the board
unnamed: Q18.1 (G), Q19.3 (D), R31.1
unnamed: Q18.2 (D), R29.2
unnamed: R14.2, R15.1, U3.5 (+INB)
OP_V1-: R5.1, U3.8 (OUTC), U3.9 (-INC)
OP_V2-: R2.1, U3.1 (OUTA), U3.2 (-INA)
OP_VS+: R2.2, R12.1, U3.12 (+IND)
OP_VS-: R5.2, R13.1, U3.13 (-IND)
PV: Q18.3 (S), R31.2; also elsewhere on the board
VREF_BIDIRECTIONAL: U3.6 (-INB), U3.7 (OUTB); also elsewhere on the board

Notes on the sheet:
The classic quad amplifier LMV324 chips below does 4 things: - 1 opamp unit to provide the half Vdd reference voltage for another opamp circuit - 2 opamp unit in buffer mode (voltage follower) for the DCDC_OUT and LOAD voltage - 1 opamp unit for the classic high side current sensing circuit (MCU_AD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
Below the shunt resistor measuring the current coming from the PV
That block is in charge to give a PV/2 to the ESP32 MCU_ADC_PV pin. That block needs MCU_ADC_PV_CTRL to be HIGH to give that voltage (power gating). Otherwise the path is blocked.
